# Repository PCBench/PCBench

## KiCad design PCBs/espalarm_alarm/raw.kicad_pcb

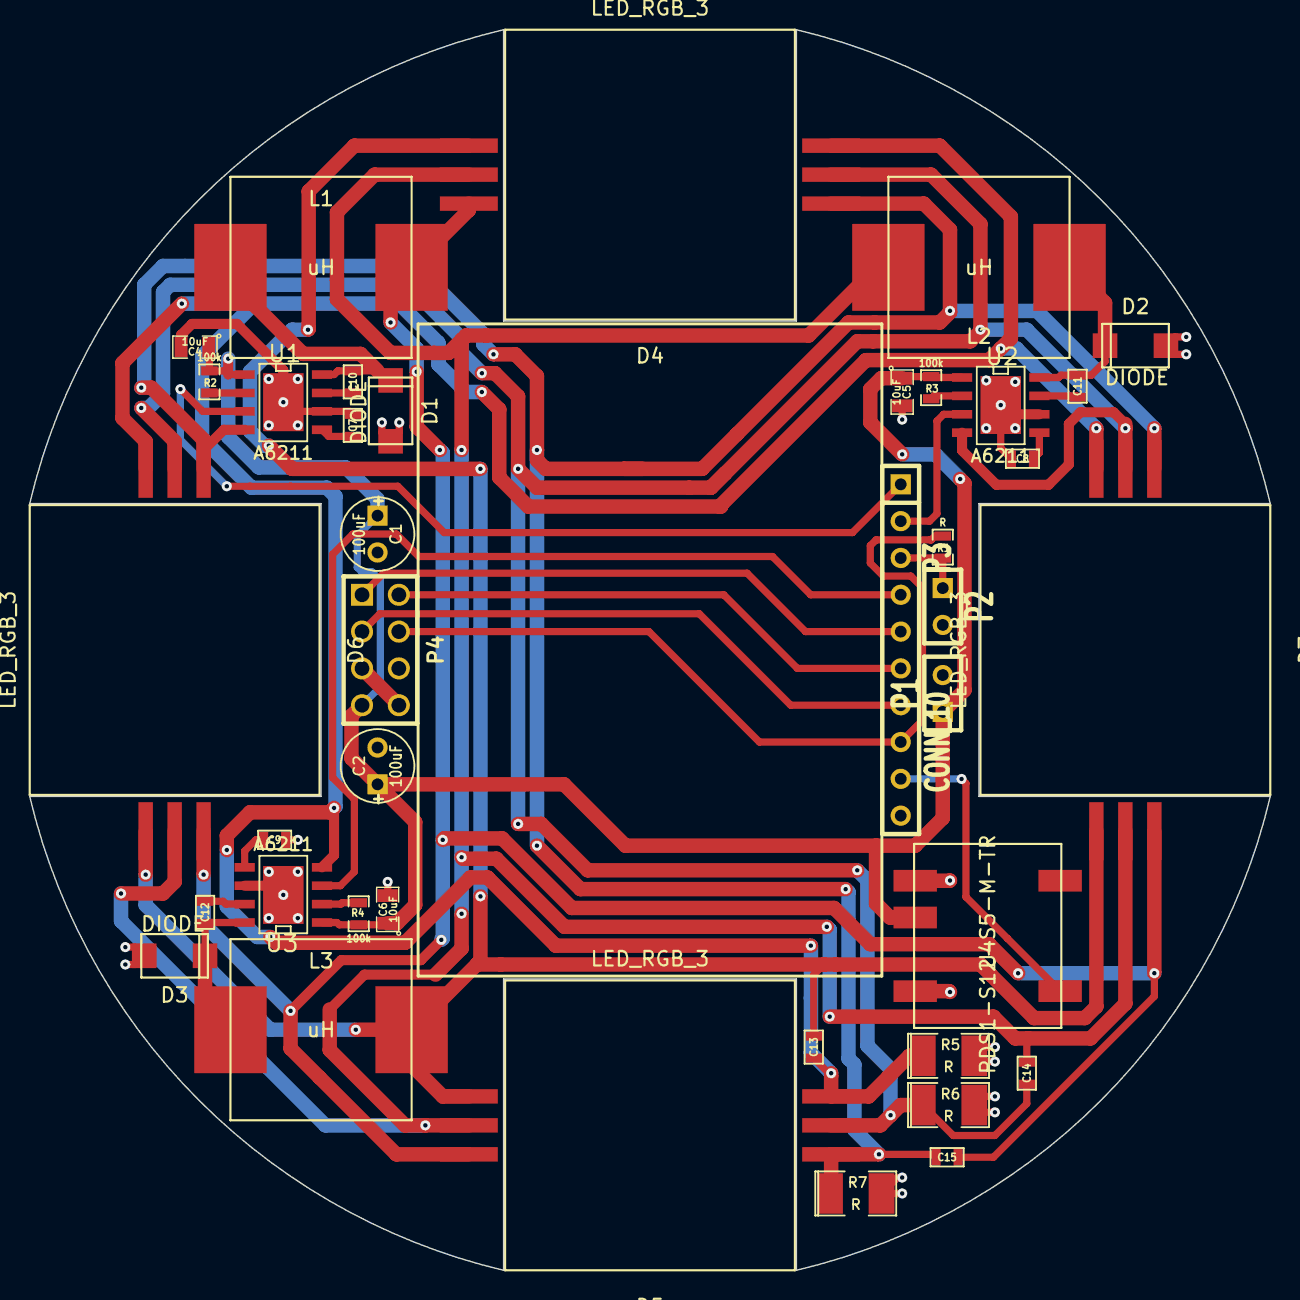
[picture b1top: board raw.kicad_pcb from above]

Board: 2 copper layers, 85.6 x 85.6 mm, 39 parts (0 on the bottom side), 29 nets.

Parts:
C1, C2: 100uF; C1V5
C4, C5, C6: 10uF; SM0805
C7, C8, C9, C10, C11, C12: 100nF; SM0603
C13, C14, C15: 1uF; SM0603
D1, D2, D3: DIODE; DIODE_SMA
D4, D5, D6, D7: LED_RGB_3; RGB_LED_10W
L1, L2, L3: uH; IND_12.5x12.5mm
P1, P2: CONN_2; SIL-2
P3: CONN_10; SIL-10
P4: CONN_8; pin_array_4x2
R1: R; SM0603_Resistor
R2, R3, R4: 100k; SM0603_Resistor
R5, R6, R7: R; SM1210L
U1, U2, U3: A6211; SO8_WITH_EP
U4: PDS1-S12-S5-M-TR

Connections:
/3.3V: P3.8, P4.4, R1.1
/5V: P3.9, U4.5
/12V: C1.1, C2.1, C4.1, C5.1, C6.1, P1.1, P4.7, R2.1, R3.1, R4.1, U1.1, U2.1, U3.1, U4.2
/GPIO0: P3.7, P4.3
/GPIO2: P3.6, P4.2
/GPIO12: P3.2, U2.3
/GPIO13: P3.4, U3.3
/GPIO14: P3.1, U1.3
/GPIO15: P3.5, P4.1
/GPIO16: P2.1, P3.3, R1.2
GND: C1.2, C2.2, C4.2, C5.2, C6.2, C7.2, C8.2, C9.2, D1.1, D2.1, D3.1, P1.2, P2.2, P3.10, P4.5, P4.8, R5.2, R6.2, R7.2, U1.6, U1.9, U2.6, U2.9, U3.6, U3.9, U4.1, U4.4
unnamed: C14.2, D4.5, D5.5, D6.5, D7.5, R6.1, U2.4
unnamed: C11.1, U2.7
unnamed: C11.2, D2.2, L2.1, U2.8
unnamed: R3.2, U2.2
unnamed: C9.1, U3.5
unnamed: R4.2, U3.2
unnamed: C8.1, U2.5
unnamed: C10.1, U1.7
unnamed: C10.2, D1.2, L1.1, U1.8
unnamed: C12.1, U3.7
unnamed: C12.2, D3.2, L3.1, U3.8
unnamed: C13.1, D4.1, D5.1, D6.1, D7.1, L3.2
unnamed: C7.1, U1.5
unnamed: C15.1, D4.3, D5.3, D6.3, D7.3, L1.2
unnamed: R2.2, U1.2
unnamed: C15.2, D4.4, D5.4, D6.4, D7.4, R7.1, U1.4
unnamed: C13.2, D4.6, D5.6, D6.6, D7.6, R5.1, U3.4
unnamed: C14.1, D4.2, D5.2, D6.2, D7.2, L2.2

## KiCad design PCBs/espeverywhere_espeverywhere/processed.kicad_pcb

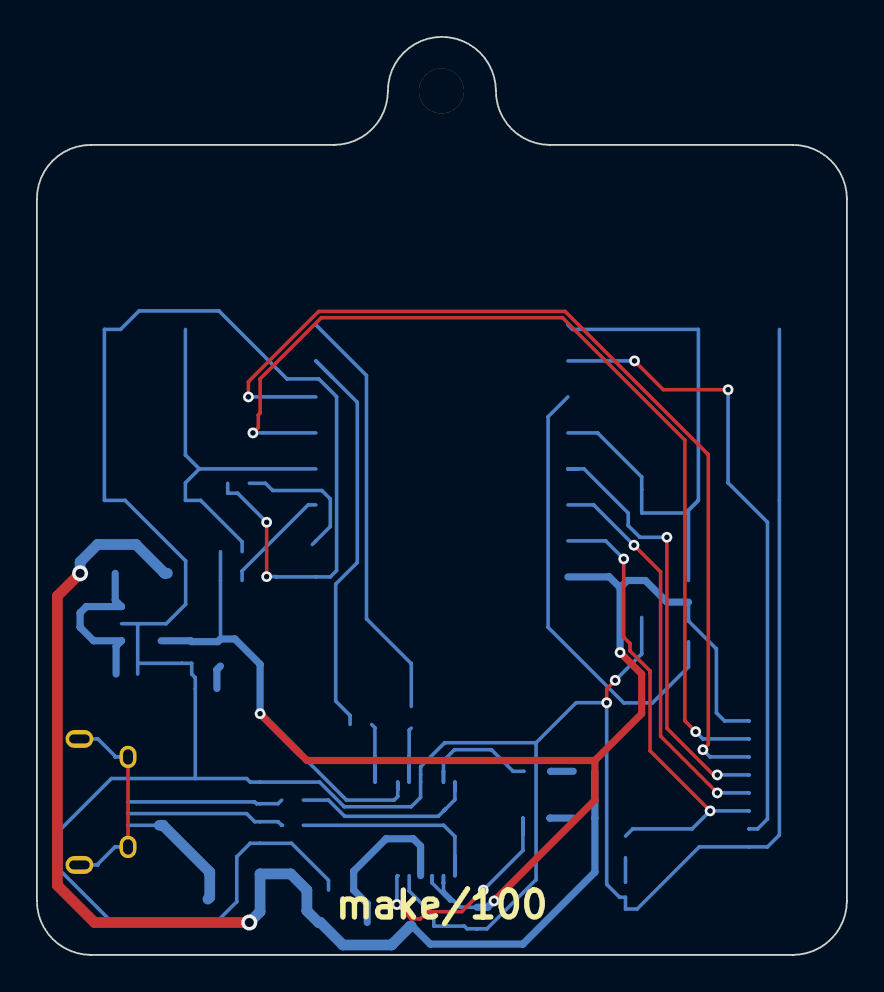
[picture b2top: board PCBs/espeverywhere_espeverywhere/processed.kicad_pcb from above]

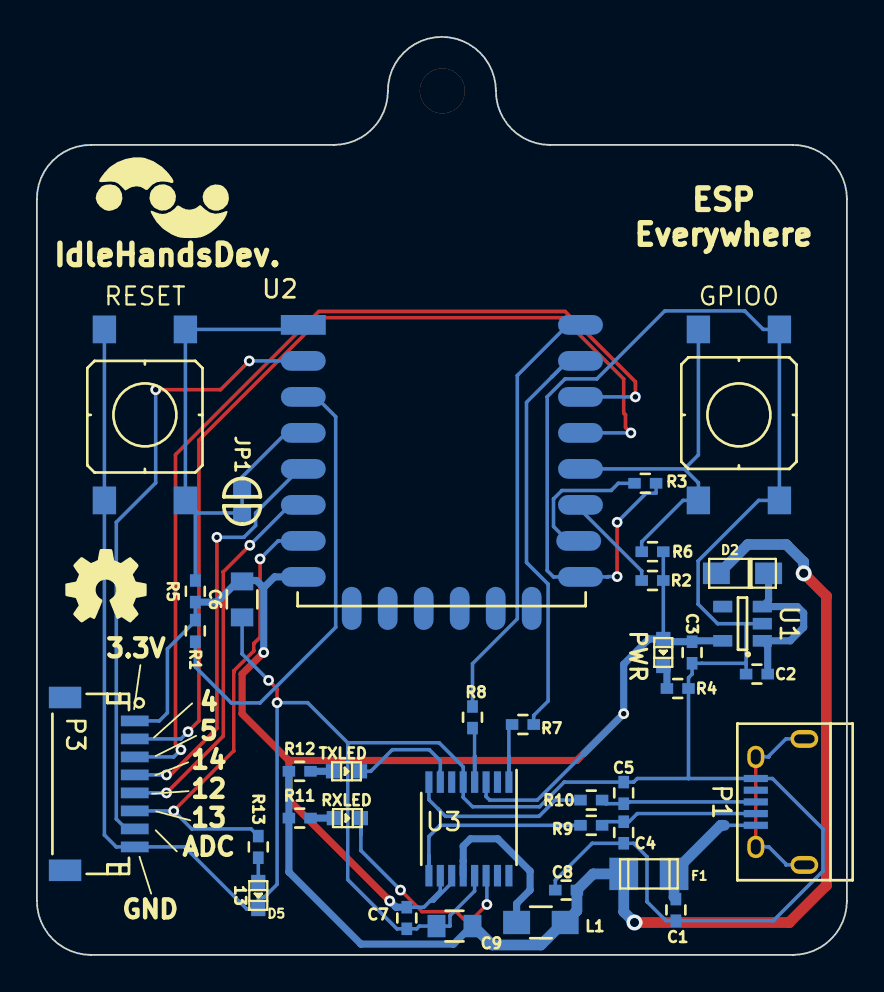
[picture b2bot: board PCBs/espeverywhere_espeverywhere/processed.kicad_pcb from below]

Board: 2 copper layers, 45.0 x 51.0 mm, 37 parts (37 on the bottom side), 31 nets.

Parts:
C1, C7, C8: 0.1uF; C_0402_Hand
C2: 1uF; C_0402_Hand
C3: 2.2uF; C_0402_Hand
C4, C5: 47pF; C_0402_Hand
C6, C9: 10uF; C_0805
D1: PWR; Led_0603
D2: BAT20J; bat20j
D3: RXLED; Led_0603
D4: TXLED; Led_0603
D5: 13; Led_0603
F1: 500mA; c_1206
JP1: Jumper_NC_Small; SOLDER-JUMPER_1-WAY-CLOSED
L1: FB; R_0805_HandSoldering
P1: USB_OTG; USB_Micro-B
P3: CONN_01X08; Connectors_JST_SM08B-SRSS-TB
R1, R2, R5: 10K; R_0402_Hand
R3, R4, R6, R7, R8, R11, R12, R13: 1K; R_0402_Hand
R9, R10: 27R; R_0402_Hand
SW2: GPIO0; Button_CKN9112CT-ND
SW3: RESET; Button_CKN9112CT-ND
U1: AP2112K-3.3V; SOT-23-5
U2: ESP-12E; ESP-12E_SMD
U3: FT230XS; SSOP-16_3.9x4.9mm_Pitch0.635mm

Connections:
+3V3: C3.1, C6.2, C7.2, D1.2, P3.1, R1.1, R2.1, R5.1, R6.1, U1.5, U2.8, U3.3, U3.10, U3.11
/ADC: P3.7, U2.2
/CH_PD: R1.2, U2.3
/GPIO0: R6.2, SW2.2, U2.18
/GPIO2: R2.2, U2.17
/GPIO4: P3.2, U2.19
/GPIO5: P3.3, U2.20
/GPIO12: P3.5, U2.6
/GPIO13: P3.6, R13.1, U2.7
/GPIO14: P3.4, U2.5
/GPIO15: R3.1, U2.16
/GPIO16: JP1.1, JP1.2, R5.2, SW3.2, U2.1, U2.4
/RXESP: R7.1, U2.21
/TXESP: R8.1, U2.22
GND: C1.1, C2.2, C3.2, C4.1, C5.1, C6.1, C7.1, C8.1, C9.1, D5.1, P1.5, P3.8, R3.2, R4.2, SW2.1, SW3.1, U1.2, U2.15, U3.5, U3.13
unnamed: C1.2, F1.2, P1.1
unnamed: C2.1, D2.1, U1.1, U1.3
unnamed: C4.2, P1.2, R9.2
unnamed: C5.2, P1.3, R10.2
unnamed: D1.1, R4.1
unnamed: D3.1, U3.14
unnamed: D3.2, R11.2
unnamed: D4.1, U3.7
unnamed: D4.2, R12.2
unnamed: D5.2, R13.2
unnamed: L1.1, U3.12
unnamed: R7.2, U3.1
unnamed: R8.2, U3.4
unnamed: R9.1, U3.9
unnamed: R10.1, U3.8
VUSB: C8.2, C9.2, D2.2, F1.1, L1.2, R11.1, R12.1

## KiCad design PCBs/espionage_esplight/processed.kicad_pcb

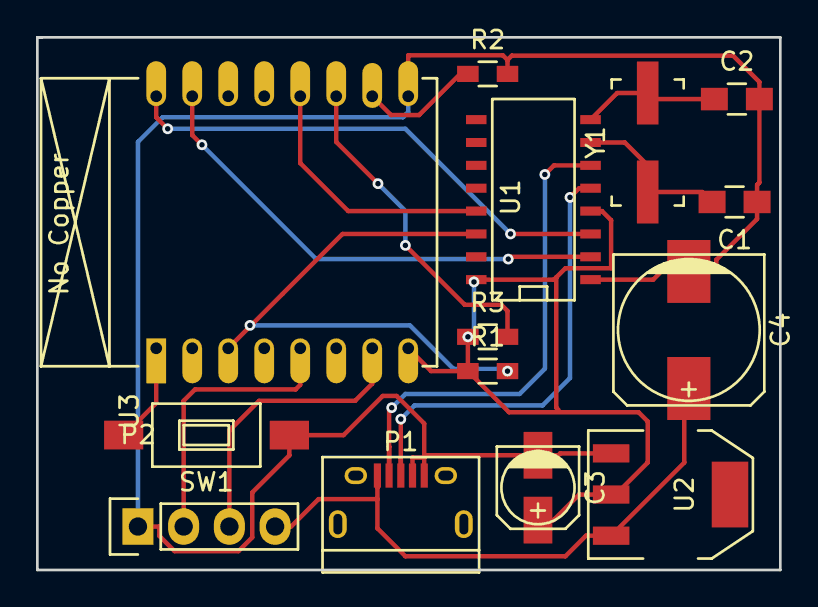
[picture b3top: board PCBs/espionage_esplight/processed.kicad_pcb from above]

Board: 2 copper layers, 41.3 x 29.6 mm, 14 parts (0 on the bottom side), 16 nets.

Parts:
C1, C2: 22pF; C_0805_HandSoldering
C3: 22uF; c_elec_4x5.8
C4: 470uF; c_elec_8x10
P1: USB_B; USB_Micro-B
P2: CONN_01X04; Socket_Strip_Straight_1x04
R1, R2, R3: 10kE; R_0603_HandSoldering
SW1: SW_PUSH; SW_SPST_FSMSM
U1: CH340G; SO-16-N
U2: AMS1117; SOT-223
U3: ESP-07v2
Y1: 20MHz; Crystal_CSM-3X_SMD

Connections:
/3.3V: C3.1, R1.1, R3.1, U1.4, U1.16, U2.2, U3.8
/5V: C4.1, P1.1, P2.4, U2.3
/CLOCK: P2.2, U3.5
/DTR: U1.13, U3.12
/GND: C1.1, C2.2, C3.2, C4.2, P1.4, P1.5, P2.1, R2.2, SW1.1, U1.1, U2.1, U3.9
/MOSI: P2.3, U3.7
/RESET: SW1.2, U3.1
/RTS: R1.2, U1.14, U3.3
/RX: U1.3, U3.16
/TX: U1.2, U3.15
unnamed: C1.2, U1.7, Y1.1
unnamed: C2.1, U1.8, Y1.2
unnamed: P1.2, U1.6
unnamed: P1.3, U1.5
unnamed: R2.1, U3.10
unnamed: R3.2, U3.11

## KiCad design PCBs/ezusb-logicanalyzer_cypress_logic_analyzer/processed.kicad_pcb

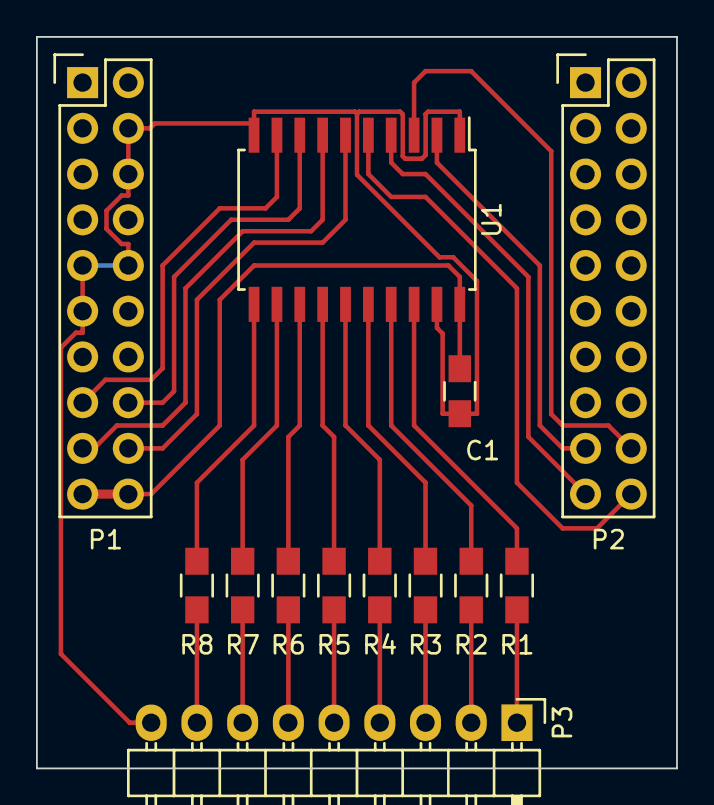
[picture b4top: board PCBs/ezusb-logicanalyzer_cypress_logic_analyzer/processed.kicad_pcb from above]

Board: 2 copper layers, 35.6 x 40.6 mm, 13 parts (0 on the bottom side), 26 nets.

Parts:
C1: .1uF; C_0805_HandSoldering
P1, P2: CONN_02X10; Pin_Header_Straight_2x10
P3: CONN_01X09; Pin_Header_Angled_1x09
R1, R2, R3, R4, R5, R6, R7, R8: 100; R_0805_HandSoldering
U1: 74LCX245; SOIC-20_7.5x12.8mm_Pitch1.27mm

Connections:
/PB0: P1.15, U1.9
/PB1: P1.16, U1.8
/PB2: P1.17, U1.7
/PB3: P1.18, U1.6
/PB4: P2.20, U1.5
/PB5: P2.19, U1.4
/PB6: P2.18, U1.3
/PB7: P2.17, U1.2
GND: C1.2, P1.4, P1.6, P1.9, P1.10, P1.11, P3.9, U1.1, U1.10, U1.19
unnamed: P3.1, R1.2
unnamed: P3.2, R2.2
unnamed: P3.3, R3.2
unnamed: P3.4, R4.2
unnamed: P3.5, R5.2
unnamed: P3.6, R6.2
unnamed: P3.7, R7.2
unnamed: P3.8, R8.2
unnamed: R1.1, U1.18
unnamed: R2.1, U1.17
unnamed: R3.1, U1.16
unnamed: R4.1, U1.15
unnamed: R5.1, U1.14
unnamed: R6.1, U1.13
unnamed: R7.1, U1.12
unnamed: R8.1, U1.11
VCC: C1.1, P1.19, P1.20, U1.20

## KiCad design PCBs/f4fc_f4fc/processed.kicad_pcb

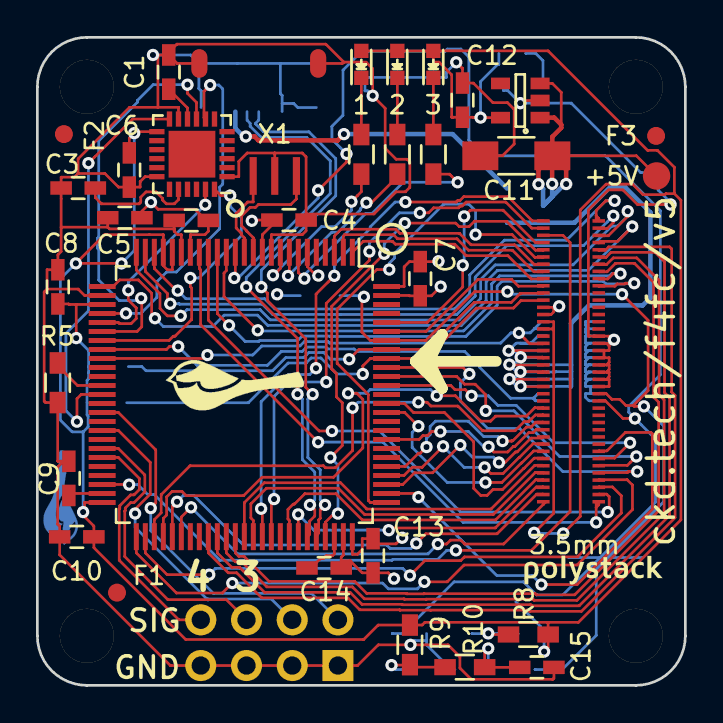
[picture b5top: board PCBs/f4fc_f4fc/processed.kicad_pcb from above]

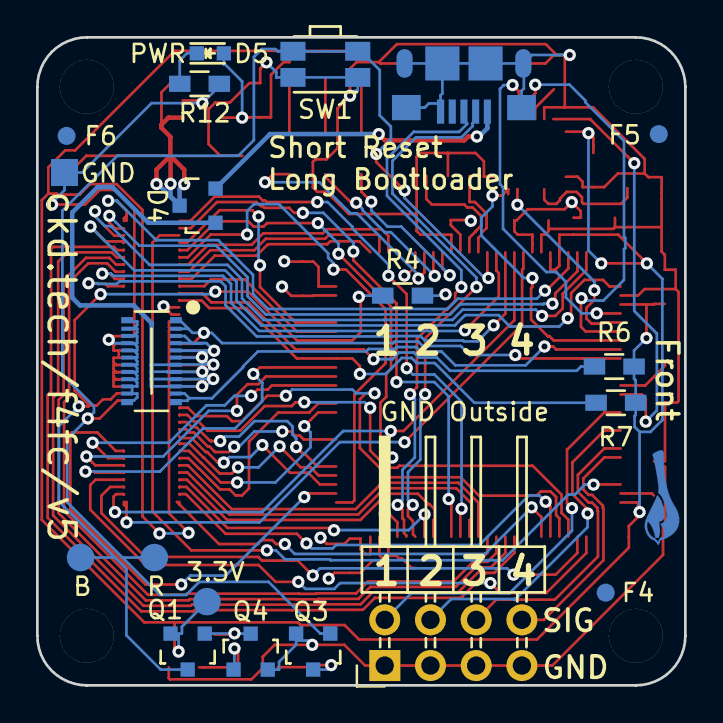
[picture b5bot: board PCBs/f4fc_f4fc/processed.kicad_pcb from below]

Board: 4 copper layers, 36.0 x 36.0 mm, 55 parts (20 on the bottom side), 81 nets.

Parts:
C1, C4, C6, C7, C8, C10, C13: 0.1uF; C_0603_HandSoldering
C2: 4.7uF; C_0603_HandSoldering
C3: 2.2nF; C_0603_HandSoldering
C5: 1uF; C_0603_HandSoldering
C9, C14, C15: 2.2uF; C_0603_HandSoldering
C11: 10uF+; C_1206_HandSoldering
C12: 1uF+; C_0603_HandSoldering
D1: Green; LED_0603
D2: Yellow; LED_0603
D3, D5: Red; LED_0603
D4: D_Schottky_x2_KCom_AAK; SOT-23
F1, F2, F3, F4, F5, F6: 1mm; Fiducial
P1: 3V3; Measurement_Point_Round-SMD-Pad_Small
P2: CONN_01X01; Measurement_Point_Square-SMD-Pad_Small
P3: USB_OTG; Mini-USB-B-EDGE
P4: CONN_02X04; Pin_Header_Angled_2x04
P5: CONN_02X10; DF40-20pin-Header
P6: RESET; Measurement_Point_Round-SMD-Pad_Small
P7: BOOT0; Measurement_Point_Round-SMD-Pad_Small
P9: 5V; Measurement_Point_Round-SMD-Pad_Small
PORT_OUT1: CKD_SANDWICH; DF40-3-4mm-80pin-Receptacle
Q1: Q_PMOS_GSD; SOT-23
Q3, Q4: Q_NMOS_GSD; SOT-23
R1, R2, R3, R12: 1k; R_0603_HandSoldering
R4, R5, R8: 10k; R_0603_HandSoldering
R6, R7: 4.7k; R_0603_HandSoldering
R9: 470k; R_0603_HandSoldering
R10: 100k; R_0603_HandSoldering
SW1: SW_PUSH; SW_SPST_EVQP7A
U1: MPU-6000; QFN-24-1EP_4x4mm_Pitch0.5mm
U2: STM32F40xxx; LQFP-100_14x14mm_Pitch0.5mm
U3: TLV70233DBV; SOT-23-5
X1: 8mhz; CSTCE_G-CSTCE_G_Z
svg2mod: G***; polystack-bold-0.4

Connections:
+5V: D4.1, P5.3, P5.5, P5.7, P5.9, P5.11, P5.13, P5.15, P5.17, PORT_OUT1.19, PORT_OUT1.20, PORT_OUT1.21, PORT_OUT1.22, PORT_OUT1.23, PORT_OUT1.24
+5VA: D4.2, P3.1
+BATT: P5.19, PORT_OUT1.18, U2.34
/ADC1: PORT_OUT1.49, U2.15
/ADC2: PORT_OUT1.50, U2.16
/GPIO1_14_SWCLK: PORT_OUT1.6, U2.76
/GPIO2_13_SWDIO: PORT_OUT1.5, U2.72
/GPIO3: PORT_OUT1.7, U2.3
/GPIO4: PORT_OUT1.8, U2.2
/GPIO5: PORT_OUT1.9, U2.1
/GPIO6: PORT_OUT1.10, U2.95
/LED0: R3.1, U2.7
/LED1: R2.1, U2.8
/LED2: R1.1, U2.9
/MPU_INT: U1.12, U2.38
/MPU_MISO: U1.9, U2.31
/MPU_MOSI: U1.24, U2.32
/MPU_NSS: U1.8, U2.29
/MPU_SCK: U1.23, U2.30
/Power/CURRENT: P5.1, U2.33
/Reset/BOOT0: P7.1, PORT_OUT1.65, Q1.3, R4.2, U2.94
/Reset/RESET: P6.1, PORT_OUT1.66, Q3.1, SW1.2, U2.14
/SPI1_MISO: PORT_OUT1.79, U2.17
/SPI1_MOSI: PORT_OUT1.80, U2.18
/SPI1_NSS: PORT_OUT1.77, U2.51
/SPI1_SCK: PORT_OUT1.78, U2.52
/SPI2_MISO: PORT_OUT1.75, U2.90
/SPI2_MOSI: PORT_OUT1.76, U2.91
/SPI2_NSS: PORT_OUT1.73, U2.77
/SPI2_SCK: PORT_OUT1.74, U2.89
/TIM1_CH1: P4.2, U2.40
/TIM1_CH2: P4.4, U2.42
/TIM1_CH3: P4.6, U2.44
/TIM1_CH4: P4.8, U2.45
/TIM2_CH4: PORT_OUT1.3, U2.48
/TIM3_CH4: PORT_OUT1.2, U2.66
/TIM8_CH3: PORT_OUT1.1, U2.65
/TIM11_CH1: PORT_OUT1.4, U2.96
/TIM12_CH1_UART8_RX: PORT_OUT1.28, U2.53
/TIM12_CH2_UART8_TX: PORT_OUT1.27, U2.54
/TIMG1_CH1: PORT_OUT1.41, U2.23
/TIMG1_CH2: PORT_OUT1.42, U2.24
/TIMG1_CH3: PORT_OUT1.43, U2.25
/TIMG1_CH4: PORT_OUT1.44, U2.26
/TIMG2_CH1: PORT_OUT1.45, U2.59
/TIMG2_CH2: PORT_OUT1.46, U2.60
/TIMG2_CH3: PORT_OUT1.47, U2.61
/TIMG2_CH4: PORT_OUT1.48, U2.62
/UART1_RX: PORT_OUT1.38, U2.69
/UART1_TX: PORT_OUT1.37, U2.68
/UART2_RX: PORT_OUT1.34, U2.87
/UART2_TX: PORT_OUT1.33, U2.86
/UART3_RX: PORT_OUT1.40, U2.56
/UART3_TX: PORT_OUT1.39, U2.55
/UART4_RX: PORT_OUT1.32, U2.79
/UART4_TX: PORT_OUT1.31, U2.78
/UART5_RX: PORT_OUT1.30, U2.83
/UART5_TX: PORT_OUT1.29, U2.80
/UART6_RX: PORT_OUT1.36, U2.64
/UART6_TX: PORT_OUT1.35, U2.63
/USB_D+: P3.3, U2.71
/USB_D-: P3.2, U2.70
/i2c_SCL: PORT_OUT1.12, R7.2, U2.92
/i2c_SDA: PORT_OUT1.11, R6.1, U2.93
GNDPWR: C1.2, C2.1, C3.1, C4.1, C5.1, C6.2, C7.1, C8.1, C9.2, C10.2, C11.2, C12.2, C13.1, C14.1, C15.2, P2.1, P3.5, P3.6, P4.1, P4.3, P4.5, P4.7, P5.2, P5.4, P5.6, P5.8, P5.10, P5.12, P5.14, P5.16, P5.18, P5.20, PORT_OUT1.13, PORT_OUT1.14, PORT_OUT1.57, PORT_OUT1.58, PORT_OUT1.59, PORT_OUT1.60, PORT_OUT1.61, PORT_OUT1.62, PORT_OUT1.63, PORT_OUT1.64, Q3.2, Q4.2, R4.1, R5.2, R12.2, SW1.1, U1.1, U1.11, U1.18, U2.10, U2.20, U2.27, U2.74, U2.99, U3.2, X1.3
unnamed: C1.1, U1.10
unnamed: C3.2, U1.20
unnamed: C9.1, U2.49
unnamed: C11.1, D4.3, P9.1, U3.1, U3.3
unnamed: C14.2, U2.73
unnamed: C15.1, Q4.1, R10.1
unnamed: D1.1, R1.2
unnamed: D2.1, R2.2
unnamed: D3.1, R3.2
unnamed: D5.1, R12.1
unnamed: Q1.1, Q4.3, R8.2
unnamed: Q3.3, R9.2, R10.2
unnamed: R5.1, U2.37
unnamed: U2.12, X1.1
unnamed: U2.13, X1.2
VDD: C2.2, C4.2, C5.2, C6.1, C7.2, C8.2, C10.1, C12.1, C13.2, D1.2, D2.2, D3.2, D5.2, P1.1, PORT_OUT1.15, PORT_OUT1.16, Q1.2, R6.2, R7.1, R8.1, R9.1, U1.13, U2.6, U2.11, U2.19, U2.21, U2.22, U2.28, U2.50, U2.75, U2.100, U3.5

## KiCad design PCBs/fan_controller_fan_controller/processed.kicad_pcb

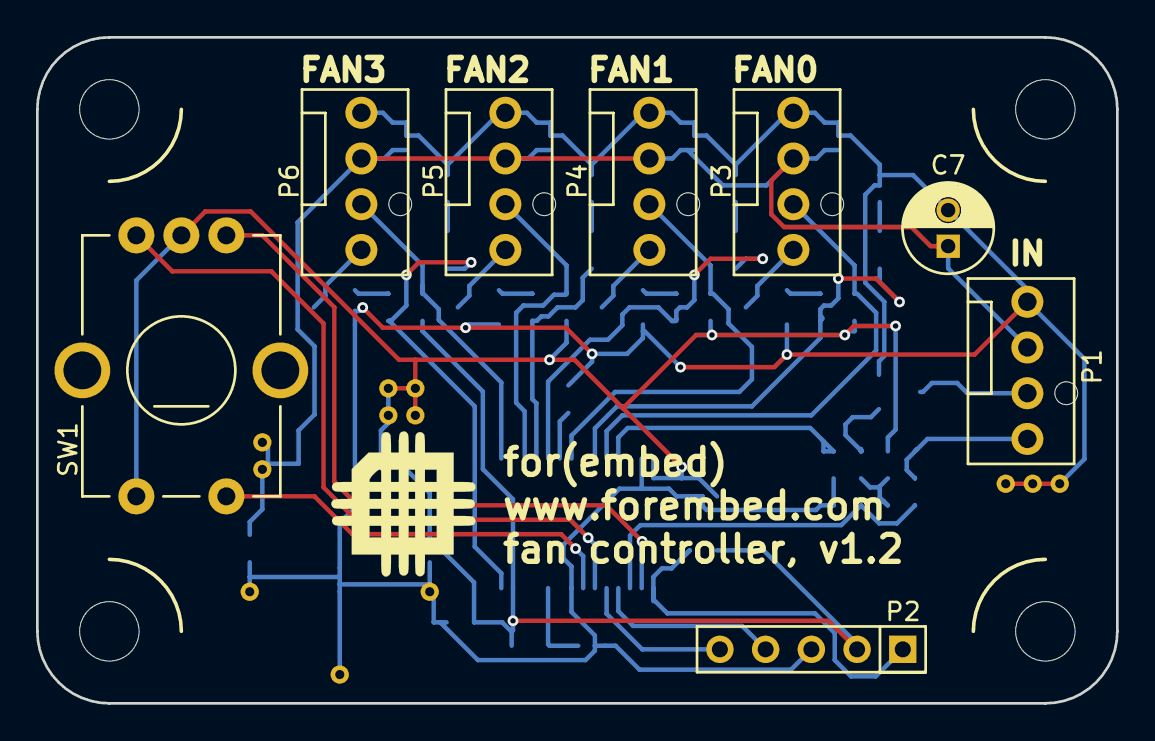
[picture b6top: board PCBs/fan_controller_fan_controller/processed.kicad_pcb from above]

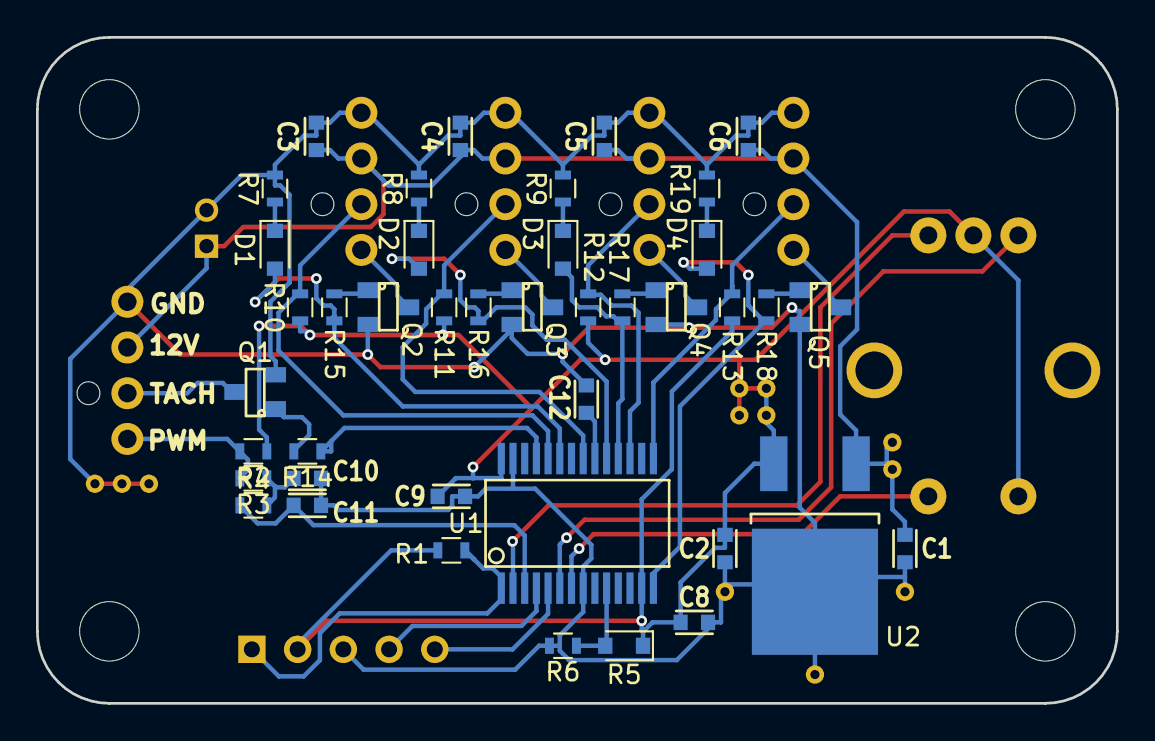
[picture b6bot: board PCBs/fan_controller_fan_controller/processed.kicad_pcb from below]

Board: 2 copper layers, 60.0 x 37.0 mm, 49 parts (41 on the bottom side), 37 nets.

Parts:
C1, C2, C3, C4, C5, C6, C8, C9, C10, C11: 100nF; SM_0603
C7: 47uF; C_Radial_D5_L11_P2
C12: 1uF; SM_0603
D1, D2, D3, D4: LED; D_0805
P1, P3, P4, P5, P6: CONN_01X04; CONN_1x4_PC_FAN
P2: CONN_01X05; CON_1x5_0.1in
Q1, Q2, Q3, Q4, Q5: Q_NPN_BEC; SOT-23
R1, R3, R4, R10, R11, R12, R13: 10k; R_0603
R2, R6, R7, R8, R9, R14, R15, R16, R17, R18, R19: 1.0k; R_0603
R5: 1k; D_0805
SW1: encoder_rotary_with_switch; encoder_EN12-HS
U1: pic24fv08km202; SSOP-28
U2: L78M05; DPAK_TO-252

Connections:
+5V: C2.1, C8.1, C9.1, P2.2, R1.1, R2.1, R5.1, R10.1, R11.1, R12.1, R13.1, SW1.2, SW1.4, U1.13, U1.28, U2.3
+12V: C1.1, C3.1, C4.1, C5.1, C6.1, C7.1, P1.2, P3.2, P4.2, P5.2, P6.2, U2.1
/ENC_A(CN2): SW1.1, U1.2
/ENC_B(CN6): SW1.3, U1.6
/SW(CN7): SW1.5, U1.7
/pwm0(OC2B): D1.2, R15.2, U1.23
/pwm1(OC5): D2.2, R16.2, U1.19
/pwm2(OC4): D3.2, R17.2, U1.18
/pwm3(OC1E): D4.2, R18.2, U1.14
/pwm_in: P1.4, R2.2, R3.2
/sense0(CN13): P3.3, R10.2, U1.24
/sense1: P4.3, R11.2, U1.21
/sense2: P5.3, R12.2, U1.17
/sense3: P6.3, R13.2, U1.15
/sense_out: P1.3, Q1.3
GND: C1.2, C2.2, C3.2, C4.2, C5.2, C6.2, C7.2, C8.2, C9.2, C10.2, C11.2, C12.2, P1.1, P2.3, P3.1, P4.1, P5.1, P6.1, Q1.2, Q2.2, Q3.2, Q4.2, Q5.2, R6.2, R7.1, R8.1, R9.1, R19.1, U1.8, U1.27, U2.2
unnamed: C10.1, R3.1, R4.2
unnamed: C12.1, U1.20
unnamed: D1.1, R7.2
unnamed: D2.1, R8.2
unnamed: D3.1, R9.2
unnamed: D4.1, R19.2
unnamed: P3.4, Q2.3
unnamed: P4.4, Q3.3
unnamed: P5.4, Q4.3
unnamed: P6.4, Q5.3
unnamed: Q1.1, R14.2
unnamed: Q2.1, R15.1
unnamed: Q3.1, R16.1
unnamed: Q4.1, R17.1
unnamed: Q5.1, R18.1
unnamed: R5.2, R6.1, U1.10
unnamed: R14.1, U1.25
PGEC: P2.5, U1.5
PGED: P2.4, U1.4
analog_cmd: C11.1, R4.1, U1.3
~MCLR: P2.1, R1.2, U1.1

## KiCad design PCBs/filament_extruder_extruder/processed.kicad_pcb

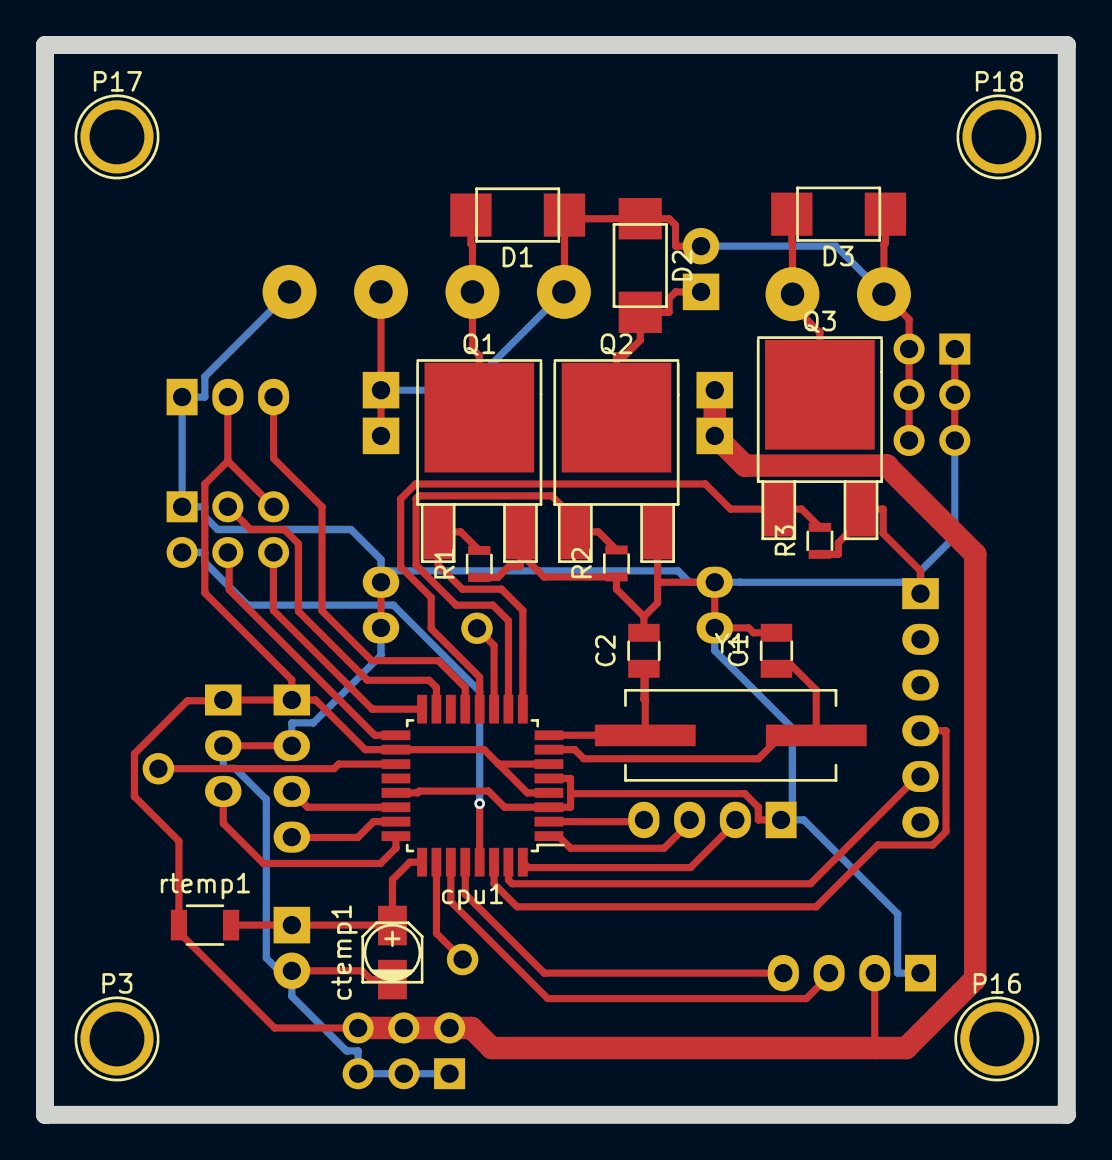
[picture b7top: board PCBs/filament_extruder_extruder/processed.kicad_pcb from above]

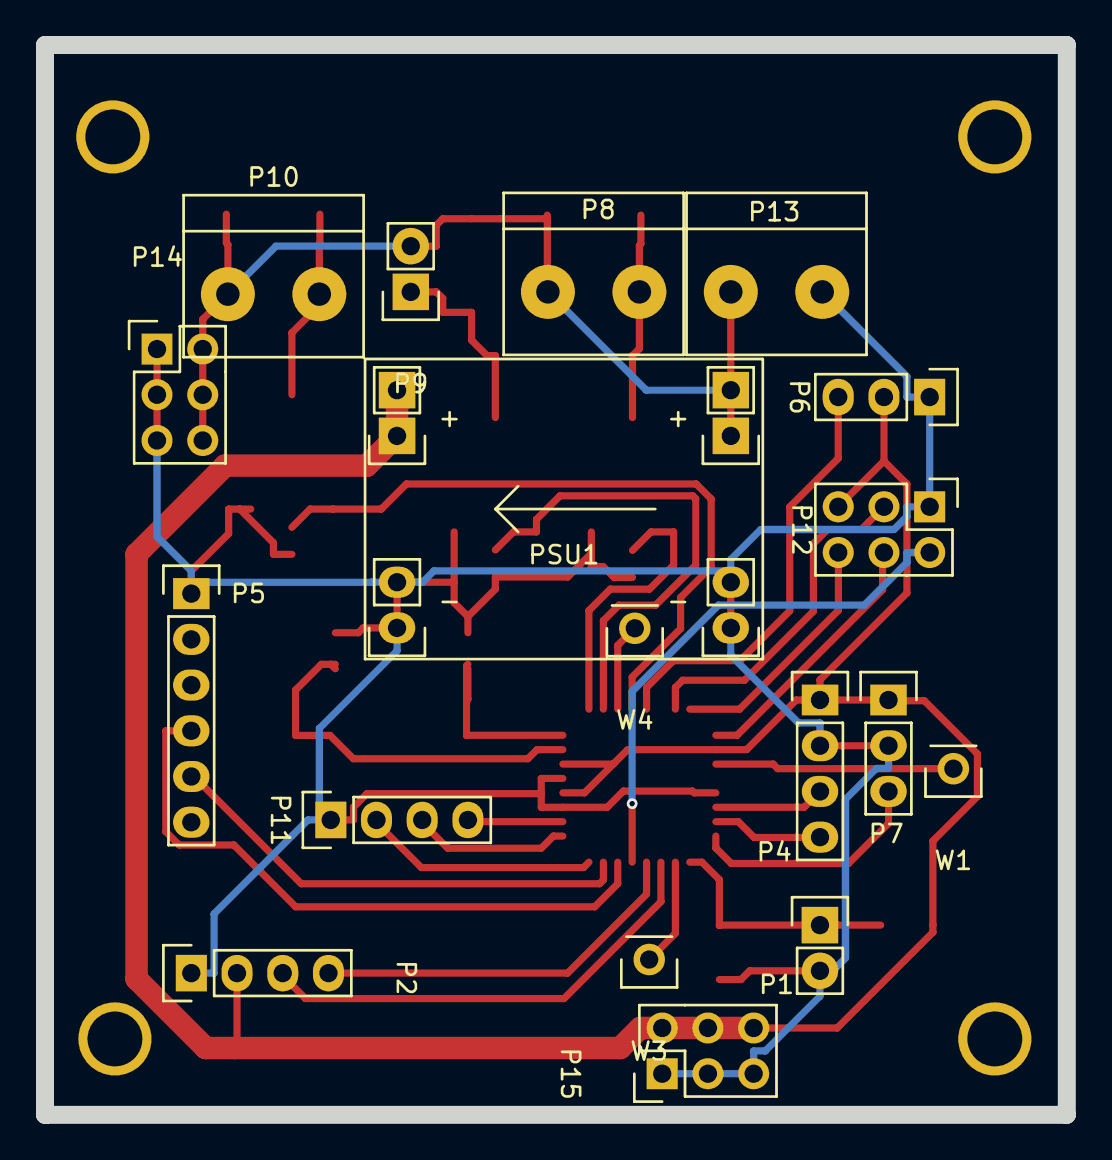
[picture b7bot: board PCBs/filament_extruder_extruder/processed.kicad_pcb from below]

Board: 2 copper layers, 56.8 x 59.4 mm, 37 parts (18 on the bottom side), 30 nets.

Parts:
C1, C2: C22pF; C_0805
D1, D2, D3: D; DO-214AC
P1: therm; Pin_Header_Straight_1x02
P2: lcd; Pin_Header_Straight_1x04
P3, P16, P17, P18: CONN_01X01; 1pin
P4: qc; Pin_Header_Straight_1x04
P5: ftdi; Pin_Header_Straight_1x06
P6: servo; Pin_Header_Straight_1x03
P7: hall; Pin_Header_Straight_1x03
P8: htr; 2Screw
P9: winder; Pin_Header_Straight_1x02
P10: auger; 2Screw
P11: enc; Pin_Header_Straight_1x04
P12: icsp; Pin_Header_Straight_2x03
P13: pwr; 2Screw
P14: 24V; Pin_Header_Straight_2x03
P15: 5V; Pin_Header_Straight_2x03
PSU1: DC-DC_Buck; 7-28V
Q1, Q2, Q3: IRLR2905PBF; TO-252-2Lead
R1, R2, R3: R100k; R_0603
W1, W3, W4: TEST_1P; Pin_Header_Straight_1x01
Y1: Crystal; Crystal_HC49-SD_SMD
cpu1: ATMEGA328P-A; TQFP-32_7x7mm_Pitch0.8mm
ctemp1: CP10uF; c_elec_3x5.3
rtemp1: R4.7k; R_1206

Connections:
+24V: D1.1, D2.1, D3.1, P8.2, P9.2, P10.2, P13.2, P14.2, P14.4, P14.6, PSU1.4
GND: C1.2, C2.2, P1.2, P2.1, P4.2, P5.1, P6.1, P7.2, P11.1, P12.1, P13.1, P14.1, P14.3, P14.5, P15.1, P15.3, P15.5, PSU1.1, PSU1.2, Q1.3, Q2.3, Q3.3, R1.1, R2.1, R3.1, cpu1.3, cpu1.5, cpu1.21, ctemp1.2
unnamed: C1.1, Y1.2, cpu1.7
unnamed: C2.1, Y1.1, cpu1.8
unnamed: D1.2, P8.1, Q1.2
unnamed: D2.2, P9.1, Q2.2
unnamed: D3.2, P10.1, Q3.2
unnamed: W1.1, cpu1.19
unnamed: W3.1, cpu1.26
unnamed: W4.1, cpu1.11
VCC: P2.2, P4.1, P6.2, P7.1, P12.5, P15.2, P15.4, P15.6, PSU1.3, cpu1.4, cpu1.6, cpu1.18, rtemp1.1
a: P11.2, cpu1.32
act: P11.4, cpu1.2
auger: Q3.1, R3.2, cpu1.12
b: P11.3, cpu1.1
diam: P4.3, cpu1.22
htr: Q1.1, R1.2, cpu1.9
length: P4.4, cpu1.23
miso: P12.6, cpu1.16
mosi: P12.3, cpu1.15
reset: P12.2, cpu1.29
rxd: P5.4, cpu1.30
sck: P12.4, cpu1.17
scl: P2.4, cpu1.28
sda: P2.3, cpu1.27
servo: P6.3, cpu1.13
spool: P7.3, cpu1.24
therm: P1.1, cpu1.25, ctemp1.1, rtemp1.2
txd: P5.5, cpu1.31
winder: Q2.1, R2.2, cpu1.10

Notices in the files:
PCBs/ezusb-logicanalyzer_cypress_logic_analyzer/processed.kicad_pcb:
Creative Commons BY-SA
PCBs/f4fc_f4fc/processed.kicad_pcb:
Copyright 2016 Chickadee Tech LLC,
This work is licensed under the Creative Commons Attribution 4.0 International License.
To view a copy of this license, visit http://creativecommons.org/licenses/by/4.0
or send a letter to Creative Commons, PO Box 1866, Mountain View, CA 94042, USA.
